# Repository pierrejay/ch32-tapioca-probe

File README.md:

# ch32-tapioca-probe

Two build-time USB debug-probe firmwares for CH32X035:

1. **CMSIS-DAP SWD + JTAG**: an ARM debug probe for OpenOCD and probe-rs.
2. **WCH-Link**: a WCH-LinkE-like probe for CH32 RISC-V, both single-wire **RVSWIO** and two-wire **RVSWD**, driven by stock minichlink or probe-rs. Auto-detects RVSWIO vs RVSWD per target.

The ~€0.25 CH32X035 needs few external parts and fits in a 3 x 3 mm QFN;
its PIOC coprocessor nicely handles the timing-critical single- and two-wire protocols,
making it practical to embed the probe directly into a product.

The project is based on [ch32fun](https://github.com/cnlohr/ch32fun) and reuses
the proven PIOC primitives from the sibling
[Tapioca](https://github.com/pierrejay/ch32-tapioca) project.

A [reference design](hardware/README.md) of a tiny <€6 probe PCB (debug/JTAG, UART bridge, 
switchable 3V3 output) is also provided with EasyEDA & KiCad source files.

## Tested

| Family | Interface | Chips | Host tools |
|---|---|---|---|
| ARM | SWD (CMSIS-DAP) | STM32H523, STM32G431 | OpenOCD, probe-rs |
| ARM | JTAG (CMSIS-DAP) | STM32H523 | OpenOCD, probe-rs |
| CH32 | RVSWIO (1-wire) | CH32V003, CH32H417 | minichlink, probe-rs |
| CH32 | RVSWD (2-wire) | CH32X035, CH32V203, CH32V307 | minichlink, probe-rs |

## Features

- **Debug transports:** ARM SWD/JTAG and WCH-Link RVSWIO/RVSWD, detailed in the
  two products below.
- **UART bridge:** optional native USB CDC ACM on USART4 (`PB0/TX`, `PB1/RX`),
  exposed as a second USB function, enabled with `make UART_BRIDGE=1` and
  configurable through the host serial port.
- **Target power:** optional load switch controlled through `PA3`; host control is
  currently available with the WCH-Link firmware.
  Switching it off releases the WCH interface and parks UART pins, avoiding
  parasitic powering of the DUT. With a self-powered DUT, `3V3` may remain
  connected; keep target power switched on to retain WCH and UART functionality.
- **Activity LED:** shows the target-power state and blinks during debug or UART
  traffic.

The debug firmwares are host-driven transports: the probe executes the
timing-critical wire transactions, while OpenOCD, probe-rs or minichlink owns
the target-specific flash algorithm.

### Product 1: CMSIS-DAP SWD + JTAG (USB `C251:F000`)

The firmware exposes one **CMSIS-DAP v2** bulk interface for ARM SWD and JTAG
with OpenOCD and probe-rs. `DAP_Connect(0)` selects SWD by default; explicit
`DAP_Connect(1)` and `DAP_Connect(2)` select SWD and JTAG respectively.

#### Pinout

The full firmware pinout supports complete SWJ-DP wiring; the minimal reference
PCB routes only the shared SWD pins:

| Signal | Pin | Notes |
|---|---|---|
| SWD `SWCLK` / JTAG `TCK` | **PC18** (PIOC IO0) | |
| SWD `SWDIO` / JTAG `TMS` | **PC19** (PIOC IO1) | shared SWJ data |
| JTAG `TDI` | PA7 | |
| JTAG `TDO` | PA6 | |
| `nSRST` / SWD `nRESET` | PA4 | optional recovery |
| JTAG `nTRST` | PA5 | optional (needs `JTAG_TRST=1`); otherwise PA5 is free |
| UART `TX` | PB0 | probe to target (needs `UART_BRIDGE=1`) |
| UART `RX` | PB1 | target to probe (needs `UART_BRIDGE=1`) |

#### Notes

- SWD runs a single fixed ~1 MHz profile (`DAP_SWJ_Clock` is accepted for host
  compatibility but doesn't change it). The ARM SWD path is validated for
  correctness, not tuned for speed; its throughput has not been benchmarked
  against a commercial probe.

- JTAG uses a GPIO engine and accepts host clock requests from 1 kHz to 2 MHz.
  Chain discovery, halt/run, reset and SRAM access were validated on STM32H523
  with both OpenOCD and probe-rs, including concurrent UART traffic. Target
  programming was validated with probe-rs at roughly 12 KiB/s. This is modest,
  but still useful for troubleshooting and recovery.

- Select the transport explicitly in the host (`--protocol swd|jtag` with
  probe-rs, or `transport select swd|jtag` with OpenOCD). SWD remains the probe's
  default when the host does not choose. On `DAP_Connect(JTAG)`, the probe emits
  the standard SWD-to-JTAG sequence so hosts such as OpenOCD 0.12 also work when
  another tool left the target in normal SWD. This best-effort transition does
  not wake a target left in the dormant state.

- `probe-rs info --protocol swd` can pause for about ten seconds after finding a
  valid DPv2 target because it deliberately probes two RP2040 multidrop
  addresses. This is a probe-rs discovery quirk, not a Tapioca transport timeout;
  normal target-specific attach and flashing are unaffected.

- Full run-control debugging works with both SWD and JTAG, not just flashing.
  RTT also works over SWD (`OpenOCD rtt` or `defmt`/probe-rs): it uses ordinary
  target-memory access and needs no trace pin.

- There is no SWO/ITM trace yet (no `DAP_SWO_*` commands), so `printf`-over-SWO and
  instruction trace aren't available.

- The CMSIS-DAP SWD and JTAG paths exercised by OpenOCD and probe-rs are
  implemented. Transfer value matching and the optional SWJ pin-wait behavior
  are not; unsupported features are not advertised as probe capabilities.

- Example OpenOCD configs for driving targets through the probe are in
  [`openocd/`](openocd/), including the validated STM32H523 JTAG chain.

### Product 2: WCH-Link, RVSWIO & RVSWD (USB `1a86:8010`)

A WCH-LinkE-compatible probe for CH32 RISC-V, driven by **stock minichlink** or
**probe-rs 0.32+** where its target support is available.

The probe implements the WCH-Link *direct-DMI* passthrough only: the **host owns the flash algorithm**, the probe just runs the wire transactions. That is simple and enough for most flashing (which is why `minichlink` drives it), but it is not a full WCH-LinkE: tools that rely on the flash-programming logic built into a real probe are untested and likely won't work as-is.

probe-rs works through this direct-DMI path and has been exercised on all targets
listed above. Support still depends on the target definitions and flash algorithms
available upstream, so less mature targets may retain host-side quirks; for example,
regular H417 flashing works, while full-chip erase awaits an upstream flash-algorithm
fix.

- **RVSWIO**: single-wire, for the small parts (CH32V003…).
- **RVSWD**: two-wire, for the larger parts (CH32V307, CH32V203, CH32X035…).
- **Auto-detection**: one firmware probes the target and picks the transport itself, so the same binary flashes a CH32V003 and a CH32V307 with no reflash.

#### Pinout

One data line, plus a clock for the 2-wire parts:

| Signal | Pin | Notes |
|---|---|---|
| `SWCLK` | **PC18** (PIOC IO0) | 2-wire only |
| `SWDIO` / `SWIO` | **PC19** (PIOC IO1) | data (1- & 2-wire) |
| UART `TX` | PB0 | probe to target (needs `UART_BRIDGE=1`) |
| UART `RX` | PB1 | target to probe (needs `UART_BRIDGE=1`) |
| `PWREN` | PA3 | target 3.3V load switch (optional, defaults on) |

#### Notes

- Some MCUs (e.g. CH32V003 1-wire and CH32X035 2-wire) drive SWDIO
  open-drain and need an external **~4.7–10 kΩ pull-up** to 3.3 V. Others (like
  CH32V203/V307) work without one. The reference board uses a 5.1 kΩ pull-up, which
  makes it universal.

- On the same direct-DMI `minichlink` it flashes ~15 % faster than a genuine WCH-LinkE
  R0-1v3 and reads ~30 % faster (CH32V203, 32 KB payload). Insignificant in practice, and not directly comparable with vendor algorithms (e.g. using wlink), but a good sign that the PIOC approach holds up. There is still plenty of headroom to optimise the USB link and flashing process.

- Some older `minichlink` builds don't drive direct-DMI. `make minichlink` builds
  the pinned version directly from the ch32fun submodule.

- Target power is controlled with `minichlink -k3 -C linke` (on) and
  `minichlink -kt -C linke` (off). The `-k` avoids probing an intentionally
  unpowered target before applying the command. Power control is not yet exposed
  by the CMSIS-DAP firmware.

## Build & flash

Clone the SDK submodule and build both products with a WCH-capable GNU RISC-V
embedded toolchain supporting `rv32imacxw` (`riscv-none-embed`,
`riscv-wch-elf`, `riscv-none-elf`, or another compatible prefix):

```sh
git submodule update --init
make
```

The Makefile uses an explicit `RISCV_PREFIX` first, then a toolchain installed
in `sdk/toolchain/`, then a compatible toolchain from `PATH`. For example, the
PlatformIO-distributed GCC 8.2.0 used to validate this project can be installed
directly in the repository without installing PlatformIO itself:

```sh
# macOS
git clone --depth 1 --branch 8.2.0 \
  https://github.com/Community-PIO-CH32V/toolchain-riscv-mac.git sdk/toolchain

# Linux x86_64, including WSL2
git clone --depth 1 --branch 8.2.0 \
  https://github.com/Community-PIO-CH32V/toolchain-riscv-linux.git sdk/toolchain
```

If the compiler has a different prefix,
pass it explicitly, for example `make RISCV_PREFIX=riscv64-unknown-elf`.

Both products flash through the CH32X035 USB ISP bootloader with
[`wchisp`](https://github.com/ch32-rs/wchisp) (hold `BOOT` while plugging in):

```sh
make flash-jtagswd   # product 1: ARM SWD/JTAG (CMSIS-DAP v2)
make flash-wchlink   # product 2: WCH-Link (auto RVSWIO/RVSWD)
```

Firmware options and the product to flash can be selected in the same command,
for example `make UART_BRIDGE=1 JTAG_TRST=1 flash-jtagswd`.
`make help` lists every supported build option and tool override.

On Linux, install the included udev rules once to access the CH32X035 ROM USB
ISP bootloader and the CMSIS-DAP development identity without `sudo` (the user
must belong to the `plugdev` group):

```sh
sudo install -m 0644 udev/50-ch32-tapioca-probe.rules /etc/udev/rules.d/
sudo udevadm control --reload-rules
```

Unplug and reconnect the probe after installing the rules.

Run the native unit tests with `make test`. See `make help` for the common
targets. PC18/PC19 are the CH32X035's own SDI debug pins, so the probe itself is
flashed over USB ISP, not SWD.

## USB identity: disclaimer

The CMSIS-DAP firmware temporarily borrows `C251:F000`, the Keil/Arm identity
used by the [CMSIS-DAP v2 example configuration](https://arm-software.github.io/CMSIS_5/DAP/html/group__DAP__ConfigUSB__gr.html).
It is not allocated to this project; CMSIS-DAP hosts identify the interface
through its `CMSIS-DAP v2` string rather than a project-specific PID.

The WCH-Link firmware still borrows WCH-LinkE's `1a86:8010` identity so stock
minichlink can discover it. This is not an official WCH, Keil or Arm product.

A dedicated [pid.codes](https://pid.codes) allocation is planned. Replace these
development identities before distributing anything built on this.

## Credits

- [**CMSIS-DAP**](https://github.com/ARM-software/CMSIS-DAP) / Arm
- [**ch32fun & minichlink**](https://github.com/cnlohr/ch32fun) / Charles Lohr

See [`THIRD_PARTY.md`](THIRD_PARTY.md) for detailed contributions.

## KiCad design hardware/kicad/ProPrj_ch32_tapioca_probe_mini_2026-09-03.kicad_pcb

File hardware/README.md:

# Reference hardware

This directory contains the reference hardware for Tapioca Probe Mini, a compact
CH32X035-based debug probe designed to plug directly into a USB-C host. It exposes
ARM SWD, JTAG and WCH RISC-V debug pins, a USB-to-UART bridge and software-controlled
3.3 V target power in a 12.5 x 23.5 mm form factor.

Fabrication files (Gerber, BOM and CPL) can be generated from the provided
EasyEDA Pro or KiCad source files.

## Board overview

- 12.5 x 23.5 mm, 4-layer PCB;
- CH32X035F8U6 in a 3 x 3 mm QFN package;
- USB-C receptacle;
- on-board RT9080-33GJ5 3.3 V regulator;
- AP2151WG-7 protected 500 mA target-power load switch, enabled by default;
- USB CDC ACM UART bridge on `PB0/TX` and `PB1/RX`;
- ARM SWD, JTAG and WCH RVSWIO/RVSWD connections;
- activity LED on `PA2`;
- switched 5.1 kOhm pull-up on `DIO`;
- ESD protection on USB and all target-facing signal lines.

Turnkey PCBA cost is around €30 for a one-shot series of five boards (shipping
excluded) using JLCPCB economic assembly. It uses the default 4-layer `7628` stackup,
compatible with economic PCBA service.

## Pinout

The board exposes eight signals on two rows of 2.54 mm through-holes. Their
layout accepts several connector options, for instance:

- conventional male or female 2.54 mm headers;
- a shrouded 04JQ-ST board-to-board plug on the four main debug signals,
  compatible with the JST-XH-style 2.50 mm connection found on inexpensive
  pogo-pin test probes, or with a small adapter board for Tag-Connect, SKEDD or
  another target connector.

The pin numbering follows the physical arrangement of the connector:

| | Signal | Signal | |
|---:|---|---|---:|
| 8 | `RXD` | `3V3` | 7 |
| 6 | `TXD` | `DIO/TMS` | 5 |
| 4 | `TDI` | `CLK/TCK` | 3 |
| 2 | `TDO` | `GND` | 1 |

For JTAG, there are no dedicated `nTRST` or `nRESET` pins;
JTAG reset uses the standard software-driven TMS sequence.

The connector labels are also printed on the bottom silkscreen:

## Target power

USB VBUS feeds the on-board RT9080-33GJ5 regulator. The probe's 3.3 V rail then
feeds the target connector through an AP2151WG-7 high-side load switch rated for
500 mA continuous current, with current limiting, short-circuit and thermal
protection.

The load switch is pulled on by default, so a target is powered immediately when
the probe starts. Firmware can switch it off when a complete DUT power cycle or
isolation is required.

In the off state, the UART pins are parked and the `DIO` pull-up is disconnected
with the target rail to prevent parasitic powering.

When the DUT has its own supply, the `3V3` connection may remain attached because
the load switch protects the probe from reverse current. Keep target power
enabled to retain the UART bridge active.

The 500 mA rating is the load-switch limit, not an unconditional target-current
budget. Available current also depends on the probe's own consumption, regulator
dissipation and the thermal limits of this small PCB.

## Entering boot mode

The PIOC occupies the CH32X035 debug pins, so the board provides two exposed pads
on the bottom side for boot-mode selection.

The USB bootloader is normally enabled at the factory, so the first upload
can be done without shorting these pads. To enter it again:

1. Disconnect the board from USB.
2. Short the pads marked **DFU** and **3V3** under the USB-C connector with
   tweezers or a small jumper. Avoid touching the USB connector shell.
3. Plug the board into USB while keeping the pads shorted; the LED should turn on.
4. Remove the short and follow the main README's
   [flashing instructions](../README.md#build--flash).

Flash commands:

```sh
make UART_BRIDGE=1 flash-wchlink # WCH RVSWIO & RVSWD
make UART_BRIDGE=1 flash-jtagswd # ARM SWD & JTAG
```

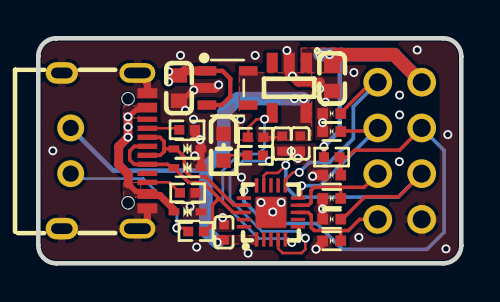
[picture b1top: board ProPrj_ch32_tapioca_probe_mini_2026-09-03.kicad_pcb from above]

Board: 4 copper layers, 23.5 x 12.5 mm, 29 parts (0 on the bottom side), 18 nets.

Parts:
C1, C3: 10uF; C0603
C2: 1uF; C0402
C4: 10uF; C0402
C29: 100nF; C0402
CN1: A2501HWR-4P; CONN-TH_A2501HWR-4P
D1, D2, D3: LESD5D5.0CT1G; SOD-523_L1.2-W0.8-LS1.6-BI
D4, D5, D6, D7, D8, D9: TPD1E01B04DPYR; X1SON-2_L1.0-W0.6-P0.65-BI
H1: PZ254R-11-04P; HDR-TH_4P-P2.54-H-M-W10.4
LED4: KT-0603R; LED-SMD_L1.6-W0.8-R-RD
R1, R2, R24, R40, R41: 5.1kΩ; R0402
R89: 1kΩ; R0402
TP1: TestPoint; Pad_e437
TP2: TestPoint; Pad_e438
U4: CH32X035F8U6; WQFN-20_L3.0-W3.0-P0.40-TL-EP1.7
U6: RT9080-33GJ5; TSOT-23-5_L2.9-W1.6-P0.95-LS2.8-BL
U9: AP2151WG-7; SOT-25-5_L3.0-W1.8-P0.95-LS3.0-BR
USB2: TYPE-C 16PIN 2MD(073); USB-C-SMD_TYPE-C-16PIN-2MD-073

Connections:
3V3: C2.2, C4.2, C29.2, R2.2, TP2.2, U4.1 (VDD), U6.5 (VOUT), U9.5 (IN)
3V3_OUT: C1.2, CN1.4, R1.2, U9.1 (OUT)
/CH32_BOOT: R24.1, TP1.1
/JTAG_TDI: D6.2, H1.2, U4.9 (PA7/MOSI/T3C2/T1C1N_/O2P0/A7)
/JTAG_TDO: D7.2, H1.1, U4.8 (PA6/MISO/T3C1/T1BK_/O1N0/A6)
/LED: R89.2, U4.4 (PA2/TX2/T2C3/O2O1/T2ET_/A2)
/PROBE_CLK: CN1.2, D5.2, U4.14 (PC18/DIO/TX3_/T2C1N_/T3C2_/I2C_)
/PROBE_DIO: CN1.3, D4.2, R1.1, U4.16 (PC19/DCK/T2C1_/T3C1_/I2C_/RX3_)
/PWSW: R2.1, U4.5 (PA3/T2C4/O1O0/T3C1_/RX2/A3), U9.4 (EN)
/UART_RX: D8.2, H1.4, U4.11 (PB1/T1C3N_/RX4/O2N1/A9)
/UART_TX: D9.2, H1.3, U4.10 (PB0/TX4/T1C2N_/O1P0/A8)
/USB_CC1: R40.1, USB2.A5 (CC1)
/USB_CC2: R41.1, USB2.B5 (CC2)
/USB_DN: D3.2, U4.17 (PC16/UDM/T1C4/TX4_/I2C_/RX4_/PC11), USB2.A7 (Dn1), USB2.B7 (Dn2)
/USB_DP: D2.2, R24.2, U4.18 (PC17/UDP/TX4_/I2C_/RX4_/T1ET/PC10), USB2.A6 (Dp1), USB2.B6 (Dp2)
GND: C1.1, C2.1, C3.1, C4.1, C29.1, CN1.1, D1.1, D2.1, D3.1, D4.1, D5.1, D6.1, D7.1, D8.1, D9.1, LED4.2 (K), R40.2, R41.2, U4.21 (GND), U6.2 (GND), U9.2 (GND), USB2.13 (EH), USB2.14 (EH), USB2.A1B12 (GND), USB2.B1A12 (GND)
unnamed: LED4.1 (A), R89.1
VBUS: C3.2, D1.2, U6.1 (VIN), U6.3 (EN), USB2.A4B9 (VBUS), USB2.B4A9 (VBUS)

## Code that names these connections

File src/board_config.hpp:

#pragma once

// Default debug pinout for the CH32X035F8U6/QFN20 reference design.
// Override these definitions through EXTRA_CPPFLAGS for a custom PCB.

// TMS/TCK share the PIOC/SDI pins used by SWDIO/SWCLK. A target wired for
// two-wire SWD can therefore use JTAG without moving those two signals.
#ifndef JTAG_TMS_PORT
#define JTAG_TMS_PORT GPIOC
#define JTAG_TMS_PIN  GPIO_Pin_19
#endif

#ifndef JTAG_TCK_PORT
#define JTAG_TCK_PORT GPIOC
#define JTAG_TCK_PIN  GPIO_Pin_18
#endif

#ifndef JTAG_TDO_PORT
#define JTAG_TDO_PORT GPIOA
#define JTAG_TDO_PIN  GPIO_Pin_6
#endif

#ifndef JTAG_TDI_PORT
#define JTAG_TDI_PORT GPIOA
#define JTAG_TDI_PIN  GPIO_Pin_7
#endif

// nSRST is shared by the JTAG and CMSIS-DAP/SWD backends.
#ifndef TARGET_RESET_PORT
#define TARGET_RESET_PORT GPIOA
#define TARGET_RESET_PIN  GPIO_Pin_4
#endif

#ifndef JTAG_SRST_PORT
#define JTAG_SRST_PORT TARGET_RESET_PORT
#define JTAG_SRST_PIN  TARGET_RESET_PIN
#endif

// Optional physical JTAG test reset. Without JTAG_TRST, the backend emulates
// nTRST through the standard TMS Test-Logic-Reset sequence instead.
#ifndef JTAG_TRST_PORT
#define JTAG_TRST_PORT GPIOA
#define JTAG_TRST_PIN  GPIO_Pin_5
#endif

#ifndef JTAG_DEFAULT_FREQUENCY_KHZ
#define JTAG_DEFAULT_FREQUENCY_KHZ 500
#endif

#ifndef LOAD_SWITCH_PIN
#define LOAD_SWITCH_PIN PA3
#endif

#ifndef LED_PIN
#define LED_PIN PA2
#endif

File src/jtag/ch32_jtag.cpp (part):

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{
    RCC->APB2PCENR |= RCC_APB2Periph_GPIOA | RCC_APB2Periph_GPIOB |
                      RCC_APB2Periph_GPIOC | RCC_APB2Periph_AFIO;
    // TCK/TMS are on PC18/PC19, the chip's SDI debug pins - free them for GPIO
    // use (idempotent; the SWD backend does the same for PIOC).
    AFIO->PCFR1 = (AFIO->PCFR1 & ~AFIO_PCFR1_SWJ_CFG) | AFIO_PCFR1_SWJ_CFG_DISABLE;

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{
    RCC->APB2PCENR |= RCC_APB2Periph_GPIOA | RCC_APB2Periph_GPIOB |
                      RCC_APB2Periph_GPIOC | RCC_APB2Periph_AFIO;
    // TCK/TMS are on PC18/PC19, the chip's SDI debug pins - free them for GPIO
    // use (idempotent; the SWD backend does the same for PIOC).
    AFIO->PCFR1 = (AFIO->PCFR1 & ~AFIO_PCFR1_SWJ_CFG) | AFIO_PCFR1_SWJ_CFG_DISABLE;

    Ch32Gpio::configure(JTAG_TCK_PORT, JTAG_TCK_PIN, GPIO_CFGLR_OUT_10Mhz_PP);
    Ch32Gpio::configure(JTAG_TDI_PORT, JTAG_TDI_PIN, GPIO_CFGLR_OUT_10Mhz_PP);
    Ch32Gpio::configure(JTAG_TMS_PORT, JTAG_TMS_PIN, GPIO_CFGLR_OUT_10Mhz_PP);
    JTAG_TDO_PORT->BCR = JTAG_TDO_PIN;
    Ch32Gpio::configure(JTAG_TDO_PORT, JTAG_TDO_PIN, GPIO_CFGLR_IN_PUPD);

    setTck(false);
    setTdi(false);
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void Ch32Jtag::disconnect()
{
    Ch32Gpio::floatPins(JTAG_TCK_PORT, JTAG_TCK_PIN);
    Ch32Gpio::floatPins(JTAG_TDI_PORT, JTAG_TDI_PIN);
    Ch32Gpio::floatPins(JTAG_TMS_PORT, JTAG_TMS_PIN);
    Ch32Gpio::floatPins(JTAG_TDO_PORT, JTAG_TDO_PIN);
    setSrst(true);
#ifdef JTAG_TRST
    setTrst(true);
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
void Ch32Jtag::setTdi(bool high)
{
    Ch32Gpio::write(JTAG_TDI_PORT, JTAG_TDI_PIN, high);
    pinState_ = static_cast<uint8_t>((pinState_ & ~0x04u) | (high ? 0x04u : 0));
}

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
bool Ch32Jtag::getTdo() const
{
    return (JTAG_TDO_PORT->INDR & JTAG_TDO_PIN) != 0;
}

void Ch32Jtag::setTrst(bool high)
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                const bool nextTdi = (sent & 0x01u) != 0;
                if (nextTdi != tdi)
                {
                    Ch32Gpio::write(JTAG_TDI_PORT, JTAG_TDI_PIN, nextTdi);
                    tdi = nextTdi;
                }
                sent >>= 1u;
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            const bool nextTdi = (sent & 0x01u) != 0;
            if (nextTdi != tdi)
            {
                Ch32Gpio::write(JTAG_TDI_PORT, JTAG_TDI_PIN, nextTdi);
                tdi = nextTdi;
            }
            sent >>= 1u;
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    uint8_t pins = 0;
    if (JTAG_TCK_PORT->INDR & JTAG_TCK_PIN) pins |= 0x01u;
    if (JTAG_TMS_PORT->INDR & JTAG_TMS_PIN) pins |= 0x02u;
    if (JTAG_TDI_PORT->INDR & JTAG_TDI_PIN) pins |= 0x04u;
    if (getTdo()) pins |= 0x08u;
#ifdef JTAG_TRST
    if (JTAG_TRST_PORT->INDR & JTAG_TRST_PIN) pins |= 0x20u;
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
